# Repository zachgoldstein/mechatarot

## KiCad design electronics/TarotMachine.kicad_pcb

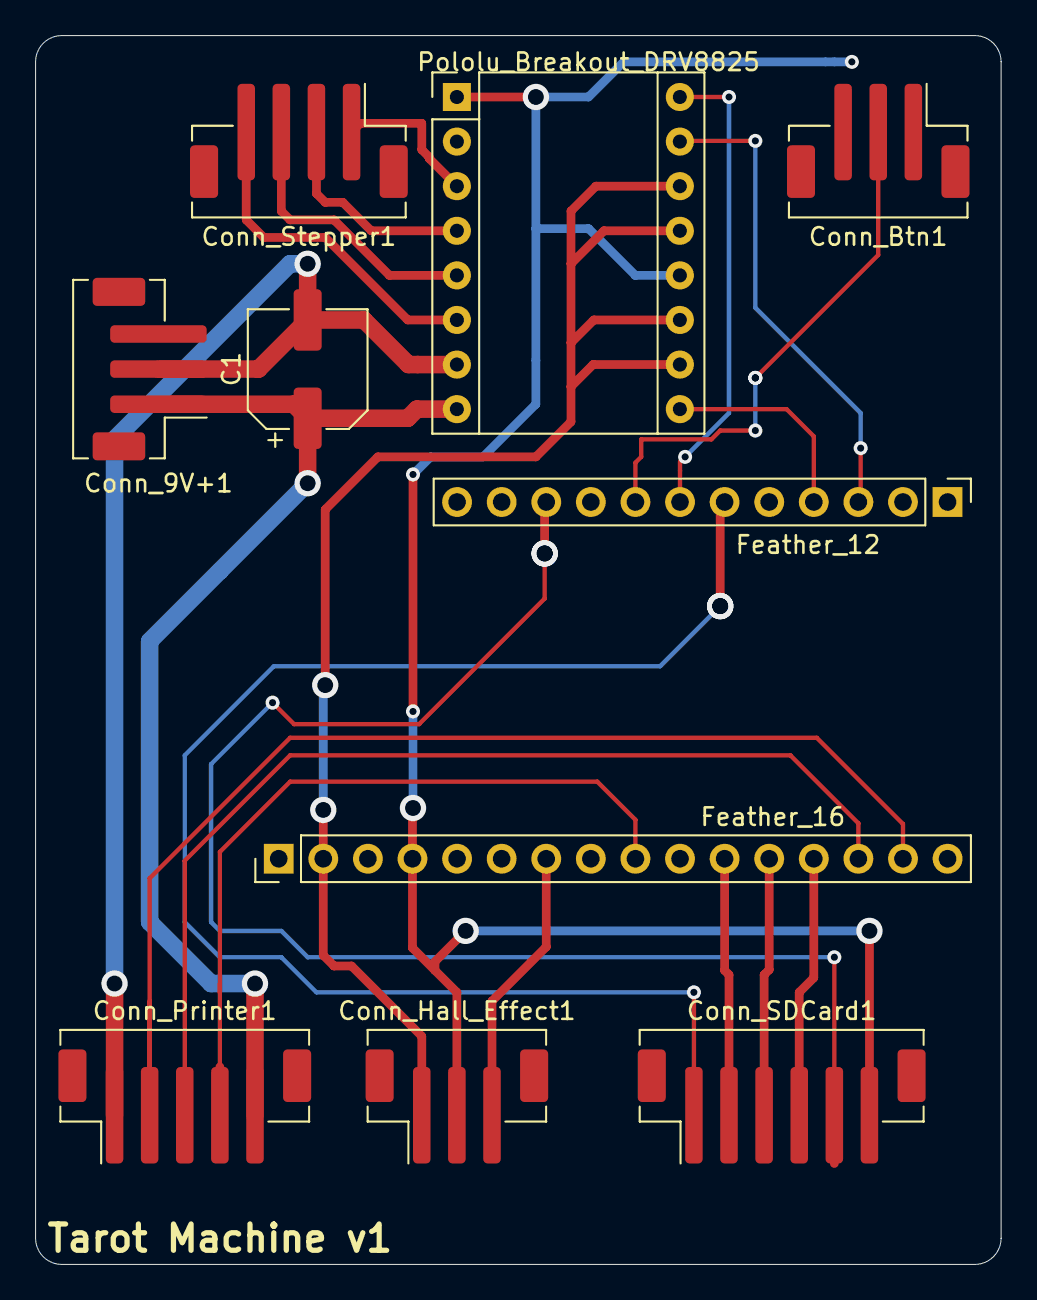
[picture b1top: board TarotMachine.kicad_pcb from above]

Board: 2 copper layers, 55.0 x 70.0 mm, 10 parts (0 on the bottom side), 21 nets.

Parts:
C1: CP_100uf; CP_Elec_6.3x5.4
Conn_9V+1: Conn_9V+; JST_PH_B3B-PH-SM4-TB_1x03-1MP_P2.00mm_Vertical
Conn_Btn1: Conn_Btn; JST_PH_B3B-PH-SM4-TB_1x03-1MP_P2.00mm_Vertical
Conn_Hall_Effect1: Conn_Hall_Effect; JST_PH_B3B-PH-SM4-TB_1x03-1MP_P2.00mm_Vertical
Conn_Printer1: Conn_Printer; JST_PH_B5B-PH-SM4-TB_1x05-1MP_P2.00mm_Vertical
Conn_SDCard1: Conn_SDCard; JST_PH_B6B-PH-SM4-TB_1x06-1MP_P2.00mm_Vertical
Conn_Stepper1: Conn_Stepper; JST_PH_B4B-PH-SM4-TB_1x04-1MP_P2.00mm_Vertical
Feather_12: Feather_12; PinHeader_1x12_P2.54mm_Vertical
Feather_16: Feather_16; PinHeader_1x16_P2.54mm_Vertical
Pololu_Breakout_DRV8825: Pololu_Breakout_DRV8825; Pololu_Breakout-16_15.2x20.3mm

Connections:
+3V3: Conn_Hall_Effect1.1, Feather_16.2, Pololu_Breakout_DRV8825.10, Pololu_Breakout_DRV8825.11, Pololu_Breakout_DRV8825.13, Pololu_Breakout_DRV8825.14
/+9V: C1.1, Conn_9V+1.1, Conn_Printer1.5, Pololu_Breakout_DRV8825.8
/GND_9V: C1.2, Conn_9V+1.2, Conn_Printer1.1, Pololu_Breakout_DRV8825.7
/GPIO_5: Feather_12.3, Pololu_Breakout_DRV8825.15
/GPIO_6: Feather_12.4, Pololu_Breakout_DRV8825.9
/GPIO_10: Conn_SDCard1.1, Feather_12.6
/GPIO_11: Feather_12.7, Pololu_Breakout_DRV8825.16
/GPIO_12: Conn_Btn1.2, Feather_12.8
/STEP_1A: Conn_Stepper1.2, Pololu_Breakout_DRV8825.4
/STEP_1B: Conn_Stepper1.3, Pololu_Breakout_DRV8825.5
/STEP_2A: Conn_Stepper1.1, Pololu_Breakout_DRV8825.3
/STEP_2B: Conn_Stepper1.4, Pololu_Breakout_DRV8825.6
/a2: Conn_Hall_Effect1.3, Feather_16.7
/a4: Conn_Printer1.4, Feather_16.9
/mi: Conn_SDCard1.4, Feather_16.13
/mo: Conn_SDCard1.3, Feather_16.12
/rx: Conn_Printer1.3, Feather_16.14
/sck: Conn_SDCard1.2, Feather_16.11
/tx: Conn_Printer1.2, Feather_16.15
/usb: Conn_SDCard1.5, Feather_12.10
GND: Conn_Btn1.1, Conn_Hall_Effect1.2, Conn_SDCard1.6, Feather_16.4, Pololu_Breakout_DRV8825.1, Pololu_Breakout_DRV8825.12

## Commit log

2022-09-23 Add content
